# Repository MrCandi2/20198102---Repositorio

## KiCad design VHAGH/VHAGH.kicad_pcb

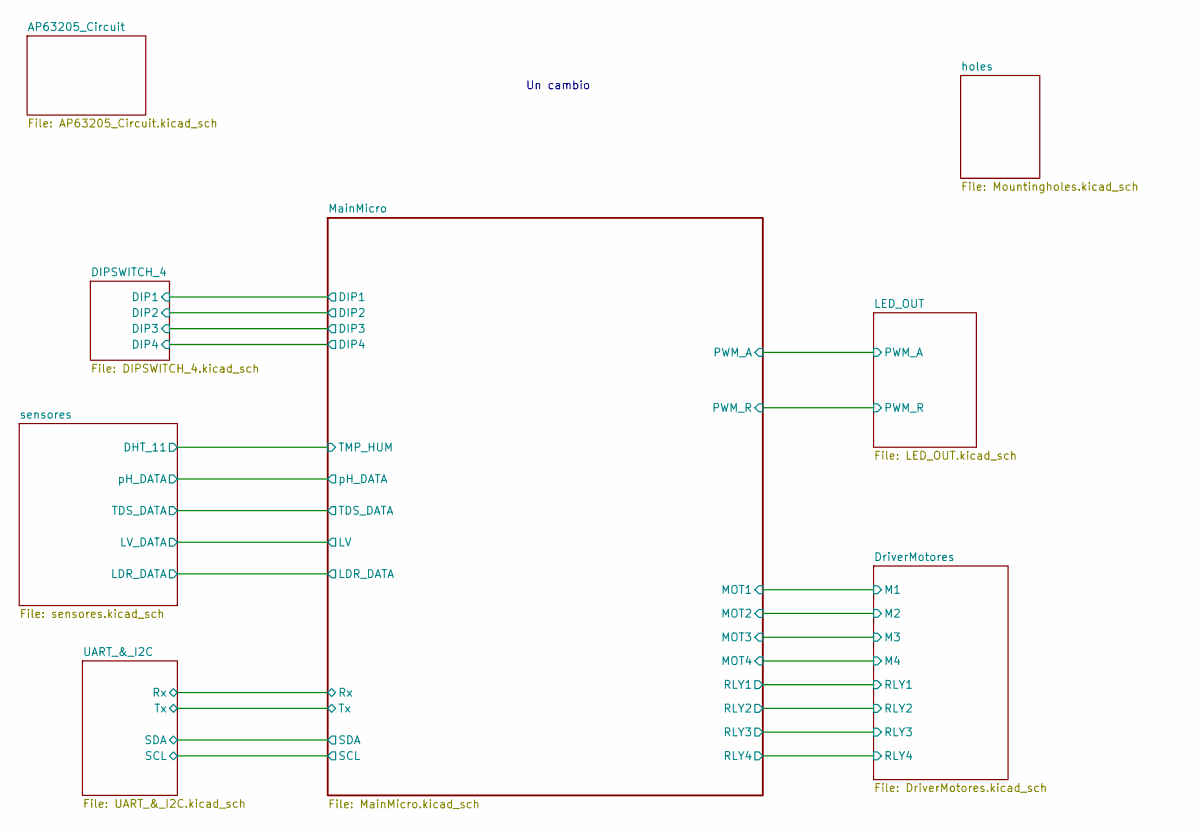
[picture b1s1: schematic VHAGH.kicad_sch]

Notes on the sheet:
Un cambio

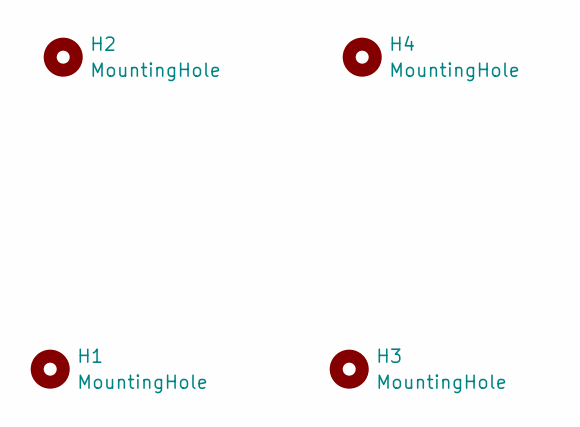
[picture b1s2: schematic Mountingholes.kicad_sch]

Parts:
H1, H2, H3, H4: MountingHole; MountingHole_2.2mm_M2

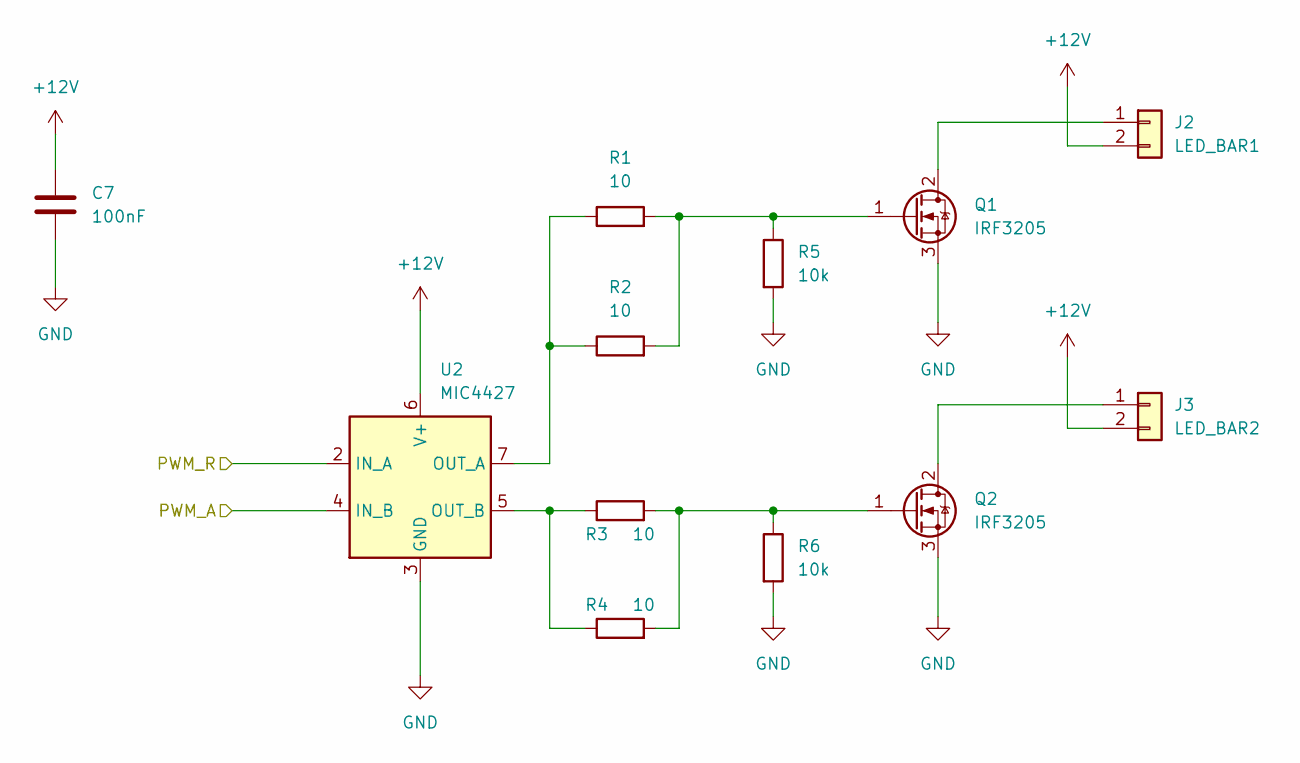
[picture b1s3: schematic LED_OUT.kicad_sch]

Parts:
C7: 100nF; C_0603_1608Metric
J2: LED_BAR1; TerminalBlock_bornier-2_P5.08mm
J3: LED_BAR2; TerminalBlock_bornier-2_P5.08mm
Q1, Q2: IRF3205; TO-220-3_Vertical
R1, R2, R3, R4: 10; R_0603_1608Metric
R5, R6: 10k; R_0603_1608Metric
U2: MIC4427; SOIC-8_3.9x4.9mm_P1.27mm

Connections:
+12V: C7.1, J2.2, J3.2, U2.6 (V+); also elsewhere on the board
/LED_OUT/PWM_A: U2.4 (IN_B); also elsewhere on the board
/LED_OUT/PWM_R: U2.2 (IN_A); also elsewhere on the board
GND: C7.2, Q1.3 (S), Q2.3 (S), R5.2, R6.2, U2.3 (GND); also elsewhere on the board
unnamed: J2.1, Q1.2 (D)
unnamed: J3.1, Q2.2 (D)
unnamed: Q1.1 (G), R1.2, R2.2, R5.1
unnamed: Q2.1 (G), R3.2, R4.2, R6.1
unnamed: R1.1, R2.1, U2.7 (OUT_A)
unnamed: R3.1, R4.1, U2.5 (OUT_B)

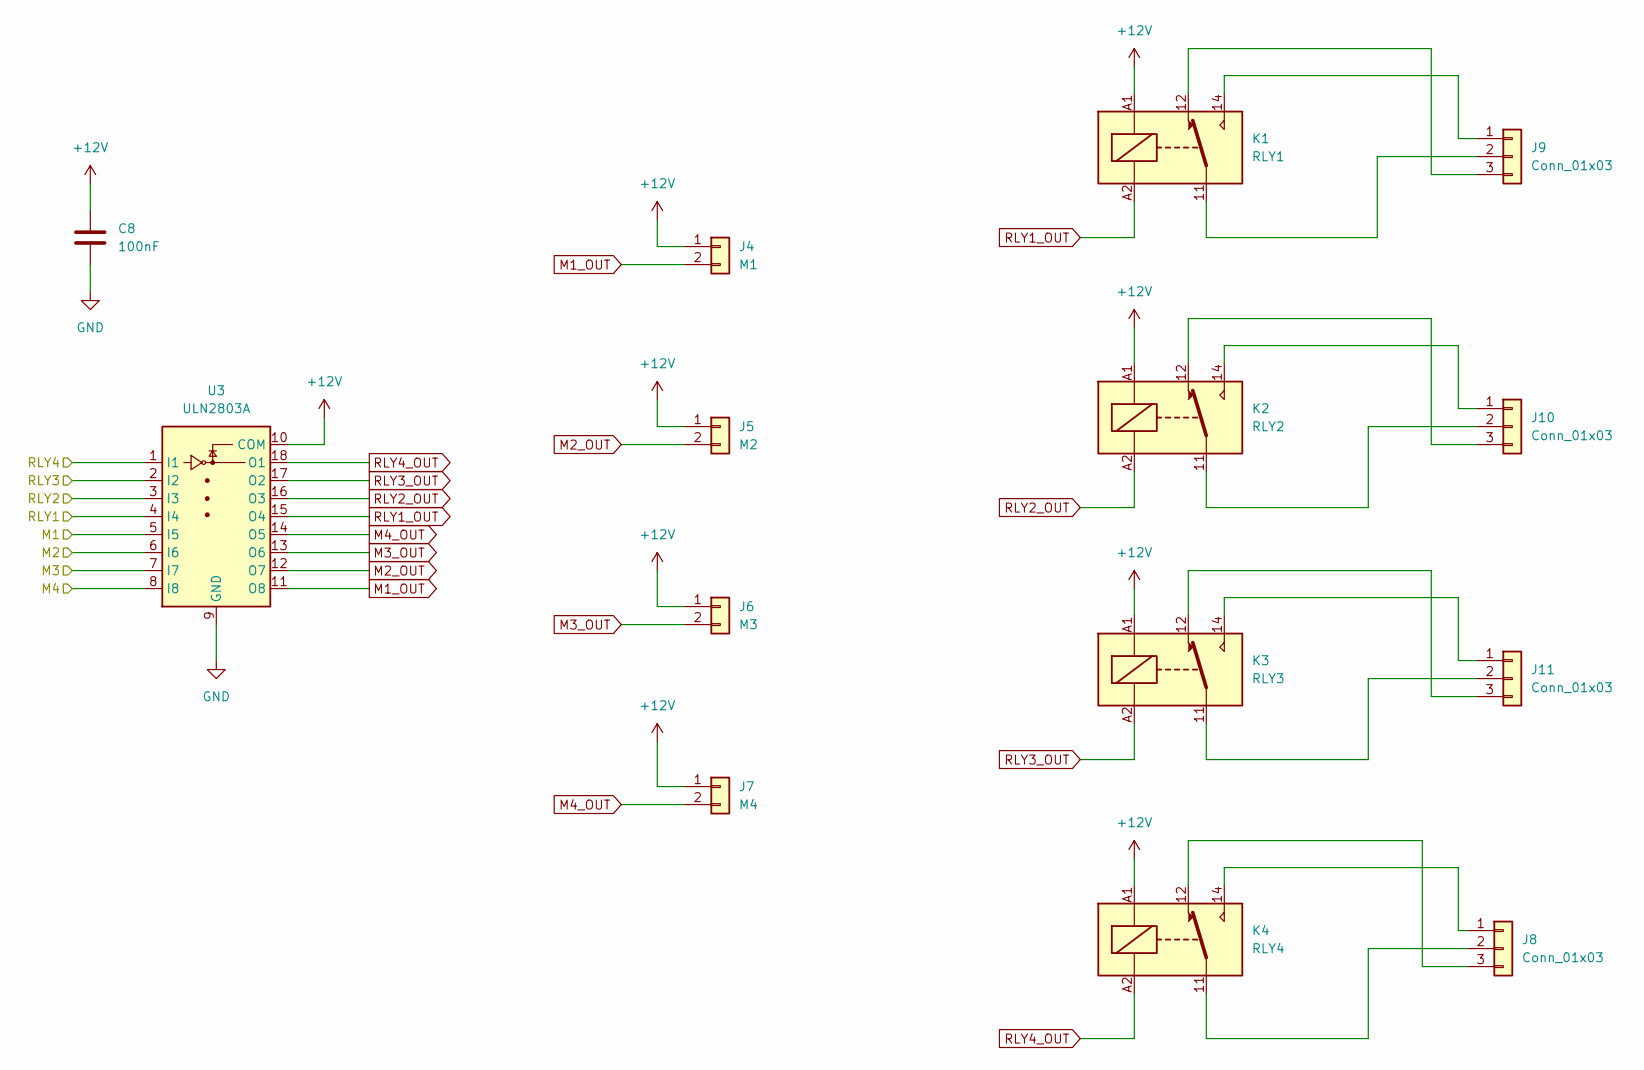
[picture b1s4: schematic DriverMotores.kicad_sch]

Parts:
C8: 100nF; C_0603_1608Metric
J4: M1; TerminalBlock_bornier-2_P5.08mm
J5: M2; TerminalBlock_bornier-2_P5.08mm
J6: M3; TerminalBlock_bornier-2_P5.08mm
J7: M4; TerminalBlock_bornier-2_P5.08mm
J8, J9, J10, J11: Conn_01x03; TerminalBlock_bornier-3_P5.08mm
K1: RLY1; Relay_SPDT_Finder_36.11
K2: RLY2; Relay_SPDT_Finder_36.11
K3: RLY3; Relay_SPDT_Finder_36.11
K4: RLY4; Relay_SPDT_Finder_36.11
U3: ULN2803A; SOIC-18W_7.5x11.6mm_P1.27mm

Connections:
+12V: C8.1, J4.1, J5.1, J6.1, J7.1, K1.A1, K2.A1, K3.A1, K4.A1, U3.10 (COM); also elsewhere on the board
/DriverMotores/M1: U3.5 (I5); also elsewhere on the board
/DriverMotores/M2: U3.6 (I6); also elsewhere on the board
/DriverMotores/M3: U3.7 (I7); also elsewhere on the board
/DriverMotores/M4: U3.8 (I8); also elsewhere on the board
/DriverMotores/RLY1: U3.4 (I4); also elsewhere on the board
/DriverMotores/RLY2: U3.3 (I3); also elsewhere on the board
/DriverMotores/RLY3: U3.2 (I2); also elsewhere on the board
/DriverMotores/RLY4: U3.1 (I1); also elsewhere on the board
GND: C8.2, U3.9 (GND); also elsewhere on the board
M1_OUT: J4.2, U3.11 (O8)
M2_OUT: J5.2, U3.12 (O7)
M3_OUT: J6.2, U3.13 (O6)
M4_OUT: J7.2, U3.14 (O5)
unnamed: J8.1, K4.14
unnamed: J8.2, K4.11
unnamed: J8.3, K4.12
unnamed: J9.1, K1.14
unnamed: J9.2, K1.11
unnamed: J9.3, K1.12
unnamed: J10.1, K2.14
unnamed: J10.2, K2.11
unnamed: J10.3, K2.12
unnamed: J11.1, K3.14
unnamed: J11.2, K3.11
unnamed: J11.3, K3.12
RLY1_OUT: K1.A2, U3.15 (O4)
RLY2_OUT: K2.A2, U3.16 (O3)
RLY3_OUT: K3.A2, U3.17 (O2)
RLY4_OUT: K4.A2, U3.18 (O1)

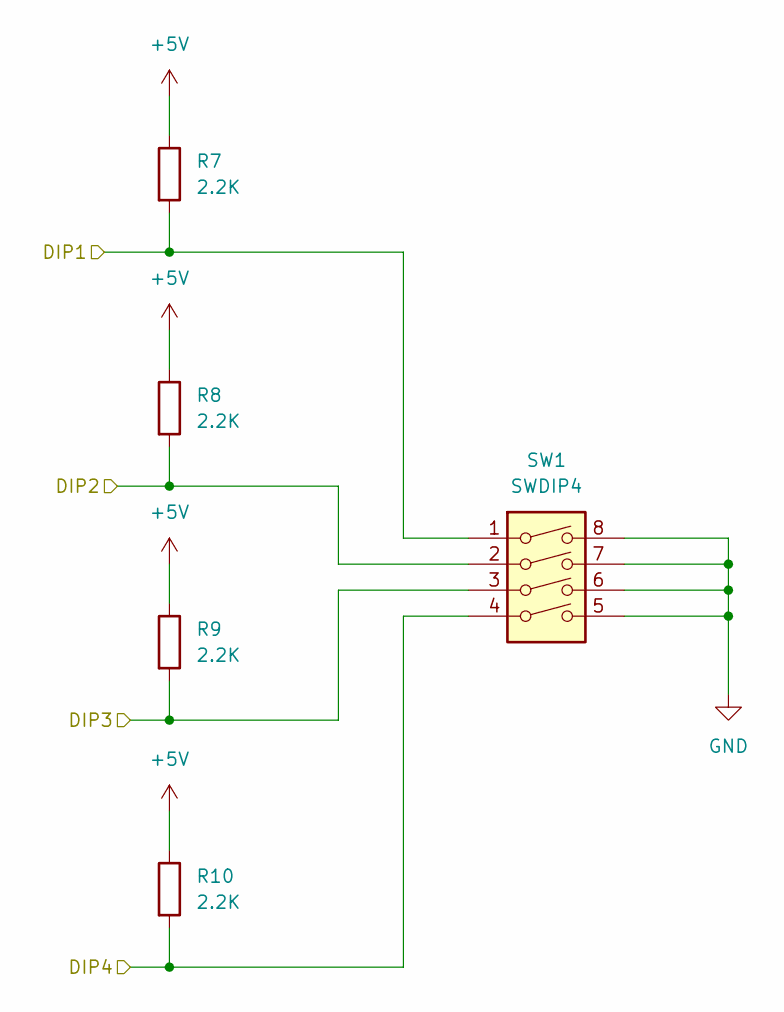
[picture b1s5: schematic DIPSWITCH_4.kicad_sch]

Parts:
R7, R8, R9, R10: 2.2K; R_0603_1608Metric
SW1: SWDIP4; SW_DIP_SPSTx04_Slide_9.78x12.34mm_W8.61mm_P2.54mm

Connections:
+5V: R7.1, R8.1, R9.1, R10.1; also elsewhere on the board
/DIPSWITCH_4/DIP1: R7.2, SW1.1; also elsewhere on the board
/DIPSWITCH_4/DIP2: R8.2, SW1.2; also elsewhere on the board
/DIPSWITCH_4/DIP3: R9.2, SW1.3; also elsewhere on the board
/DIPSWITCH_4/DIP4: R10.2, SW1.4; also elsewhere on the board
GND: SW1.5, SW1.6, SW1.7, SW1.8; also elsewhere on the board

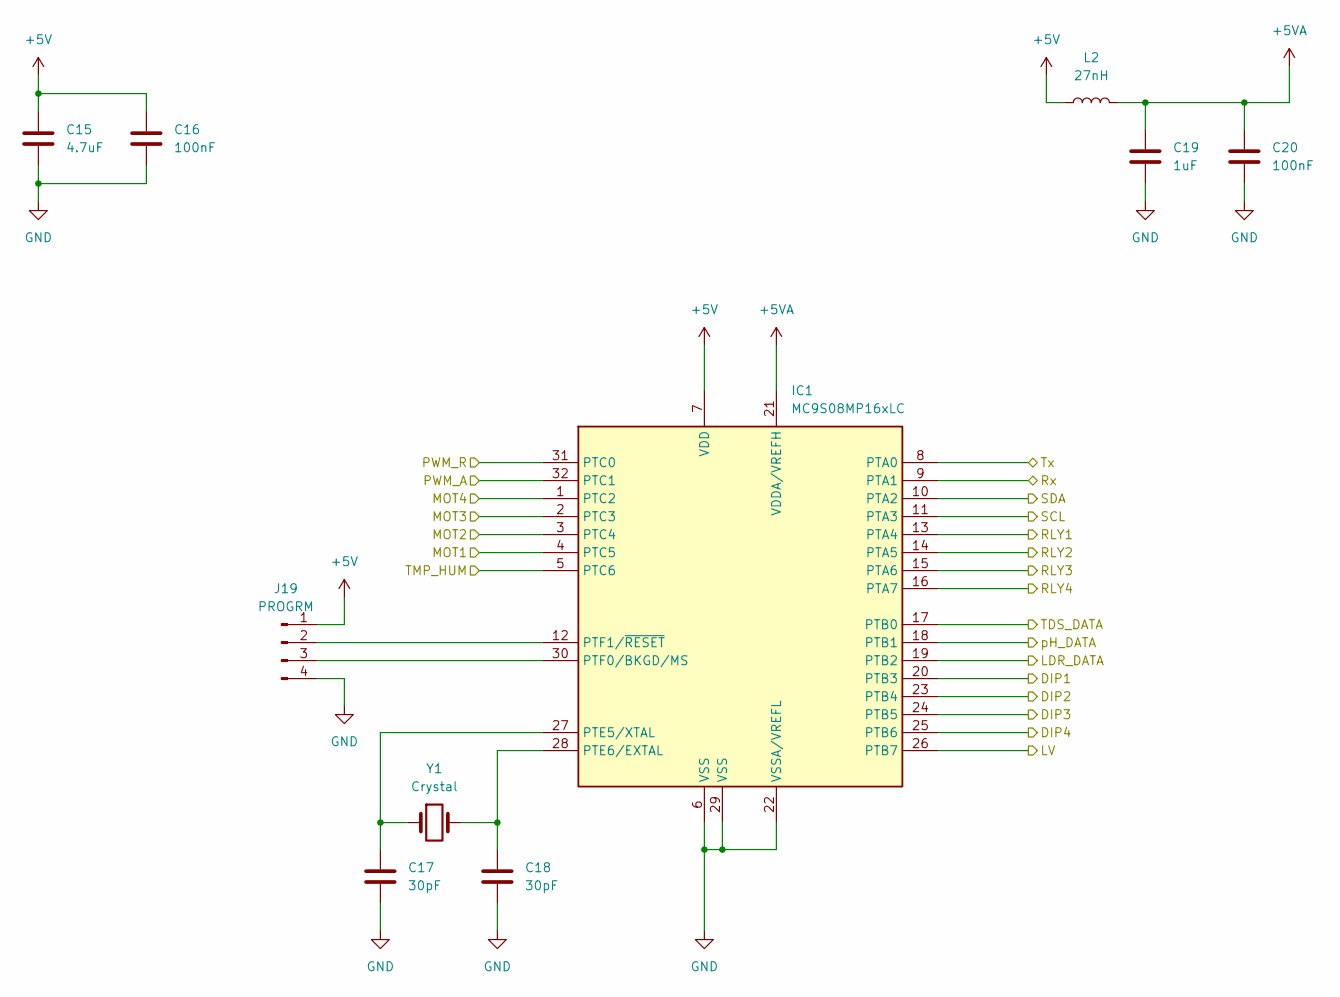
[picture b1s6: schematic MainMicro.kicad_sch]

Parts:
C15: 4.7uF; C_0603_1608Metric
C16, C20: 100nF; C_0603_1608Metric
C17, C18: 30pF; C_0603_1608Metric
C19: 1uF; C_0603_1608Metric
IC1: MC9S08MP16xLC; LQFP-32_7x7mm_P0.8mm
J19: PROGRM; PinHeader_1x04_P2.54mm_Vertical
L2: 27nH; L_0805_2012Metric
Y1: Crystal; Crystal_SMD_2012-2Pin_2.0x1.2mm

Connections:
+5V: C15.1, C16.1, IC1.7 (VDD), J19.1, L2.1; also elsewhere on the board
+5VA: C19.1, C20.1, IC1.21 (VDDA/VREFH), L2.2
/DIPSWITCH_4/DIP1: IC1.20 (PTB3); also elsewhere on the board
/DIPSWITCH_4/DIP2: IC1.23 (PTB4); also elsewhere on the board
/DIPSWITCH_4/DIP3: IC1.24 (PTB5); also elsewhere on the board
/DIPSWITCH_4/DIP4: IC1.25 (PTB6); also elsewhere on the board
/DriverMotores/M1: IC1.4 (PTC5); also elsewhere on the board
/DriverMotores/M2: IC1.3 (PTC4); also elsewhere on the board
/DriverMotores/M3: IC1.2 (PTC3); also elsewhere on the board
/DriverMotores/M4: IC1.1 (PTC2); also elsewhere on the board
/DriverMotores/RLY1: IC1.13 (PTA4); also elsewhere on the board
/DriverMotores/RLY2: IC1.14 (PTA5); also elsewhere on the board
/DriverMotores/RLY3: IC1.15 (PTA6); also elsewhere on the board
/DriverMotores/RLY4: IC1.16 (PTA7); also elsewhere on the board
/LED_OUT/PWM_A: IC1.32 (PTC1); also elsewhere on the board
/LED_OUT/PWM_R: IC1.31 (PTC0); also elsewhere on the board
/MainMicro/LDR_DATA: IC1.19 (PTB2); also elsewhere on the board
/MainMicro/LV: IC1.26 (PTB7); also elsewhere on the board
/MainMicro/Rx: IC1.9 (PTA1); also elsewhere on the board
/MainMicro/SCL: IC1.11 (PTA3); also elsewhere on the board
/MainMicro/SDA: IC1.10 (PTA2); also elsewhere on the board
/MainMicro/TDS_DATA: IC1.17 (PTB0); also elsewhere on the board
/MainMicro/TMP_HUM: IC1.5 (PTC6); also elsewhere on the board
/MainMicro/Tx: IC1.8 (PTA0); also elsewhere on the board
/MainMicro/pH_DATA: IC1.18 (PTB1); also elsewhere on the board
GND: C15.2, C16.2, C17.2, C18.2, C19.2, C20.2, IC1.6 (VSS), IC1.22 (VSSA/VREFL), IC1.29 (VSS), J19.4; also elsewhere on the board
unnamed: C17.1, IC1.27 (PTE5/XTAL), Y1.1
unnamed: C18.1, IC1.28 (PTE6/EXTAL), Y1.2
unnamed: IC1.12 (PTF1/~RESET), J19.2
unnamed: IC1.30 (PTF0/BKGD/MS), J19.3

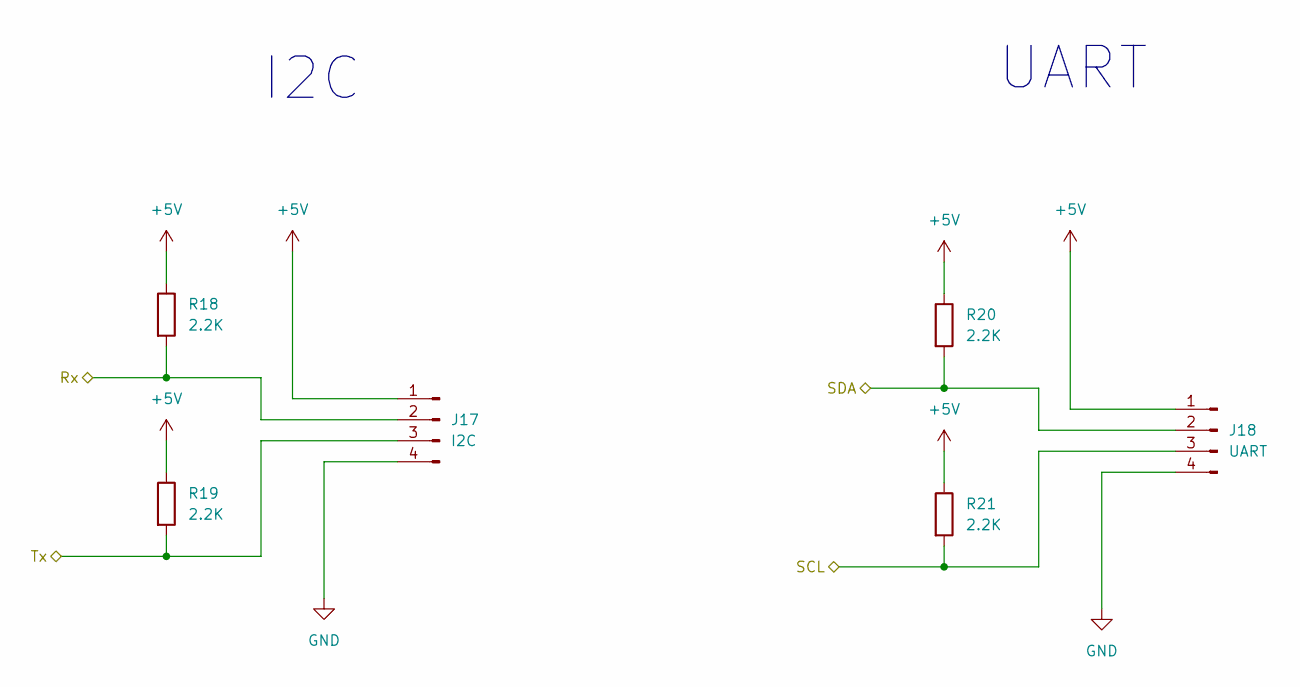
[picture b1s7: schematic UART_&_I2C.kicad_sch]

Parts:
J17: I2C; PinHeader_1x04_P2.54mm_Vertical
J18: UART; PinHeader_1x04_P2.54mm_Vertical
R18, R19, R20, R21: 2.2K; R_0603_1608Metric

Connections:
+5V: J17.1, J18.1, R18.1, R19.1, R20.1, R21.1; also elsewhere on the board
/MainMicro/Rx: J17.2, R18.2; also elsewhere on the board
/MainMicro/SCL: J18.3, R21.2; also elsewhere on the board
/MainMicro/SDA: J18.2, R20.2; also elsewhere on the board
/MainMicro/Tx: J17.3, R19.2; also elsewhere on the board
GND: J17.4, J18.4; also elsewhere on the board

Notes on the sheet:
I2C
UART

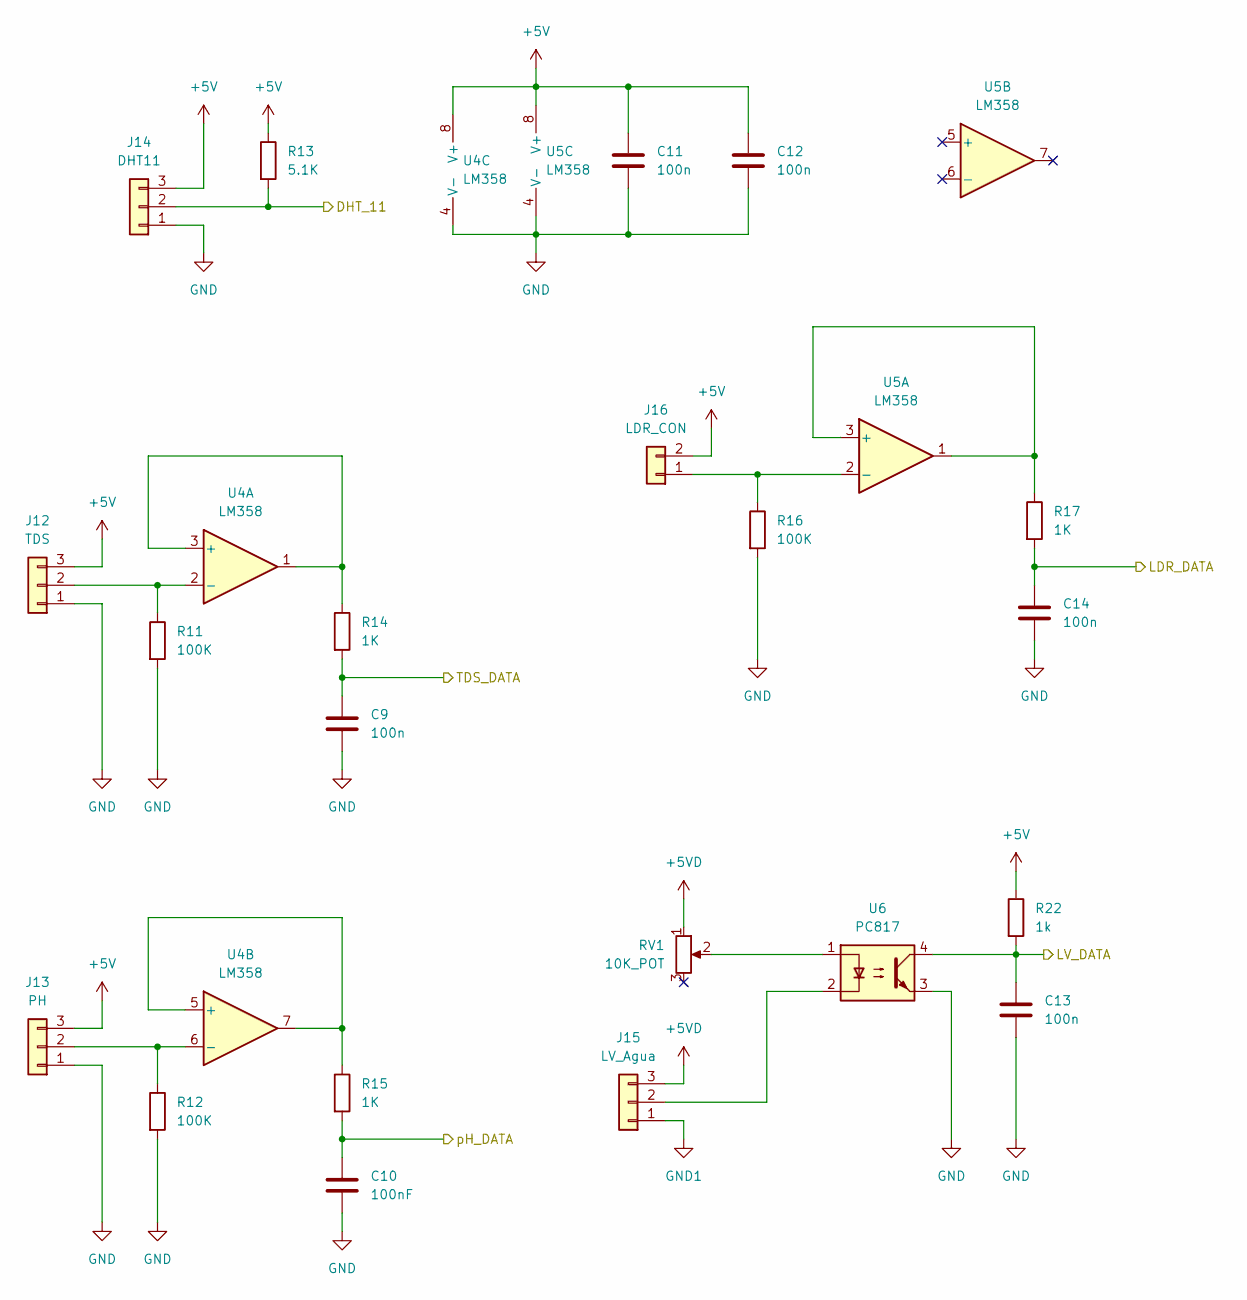
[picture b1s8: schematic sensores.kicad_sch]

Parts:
C9, C11, C12, C13, C14: 100n; C_0603_1608Metric
C10: 100nF; C_0603_1608Metric
J12: TDS; TerminalBlock_bornier-3_P5.08mm
J13: PH; TerminalBlock_bornier-3_P5.08mm
J14: DHT11; TerminalBlock_bornier-3_P5.08mm
J15: LV_Agua; TerminalBlock_bornier-3_P5.08mm
J16: LDR_CON; TerminalBlock_bornier-2_P5.08mm
R11, R12, R16: 100K; R_0603_1608Metric
R13: 5.1K; R_0603_1608Metric
R14, R15, R17: 1K; R_0603_1608Metric
R22: 1k; R_0603_1608Metric
RV1: 10K_POT; Potentiometer_Alps_RK097_Single_Horizontal
U4, U5: LM358; SOIC-8_3.9x4.9mm_P1.27mm
U6: PC817; DIP-4_W7.62mm

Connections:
+5V: C11.1, C12.1, J12.3, J13.3, J14.3, J16.2, R13.1, R22.1, U4.8 (V+), U5.8 (V+); also elsewhere on the board
+5VD: J15.3, RV1.1
/MainMicro/LDR_DATA: C14.1, R17.2; also elsewhere on the board
/MainMicro/LV: C13.1, R22.2, U6.4; also elsewhere on the board
/MainMicro/TDS_DATA: C9.1, R14.2; also elsewhere on the board
/MainMicro/TMP_HUM: J14.2, R13.2; also elsewhere on the board
/MainMicro/pH_DATA: C10.1, R15.2; also elsewhere on the board
GND: C9.2, C10.2, C11.2, C12.2, C13.2, C14.2, J12.1, J13.1, J14.1, R11.2, R12.2, R16.2, U4.4 (V-), U5.4 (V-), U6.3; also elsewhere on the board
GND1: J15.1
unnamed: J12.2, R11.1, U4.2 (-)
unnamed: J13.2, R12.1, U4.6 (-)
unnamed: J15.2, U6.2
unnamed: J16.1, R16.1, U5.2 (-)
unnamed: R14.1, U4.1, U4.3 (+)
unnamed: R15.1, U4.5 (+), U4.7
unnamed: R17.1, U5.1, U5.3 (+)
unnamed: RV1.2, U6.1

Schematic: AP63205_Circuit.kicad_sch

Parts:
C1: 10uF; C_0603_1608Metric
C2, C5, C6: 100nF; C_0603_1608Metric
C3, C4: 22uF; C_0603_1608Metric
J1: +12V; TerminalBlock_bornier-2_P5.08mm
L1: u.7uH; L_0805_2012Metric
U1: AP63205WU; TSOT-23-6

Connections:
+5V: C3.1, C4.1, C5.1, C6.1, L1.2, U1.1 (FB); also elsewhere on the board
+12V: C1.1, J1.2, U1.2 (EN), U1.3 (IN); also elsewhere on the board
GND: C1.2, C3.2, C4.2, C5.2, C6.2, J1.1, U1.4 (GND); also elsewhere on the board
unnamed: C2.1, L1.1, U1.5 (SW)
unnamed: C2.2, U1.6 (BST)

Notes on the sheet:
Capacitor ceramico es suficiente Capacitor low ESR recomendado para minimizar pérdidas
2A Continous Output Current
Capacitor ceramico es suficiente

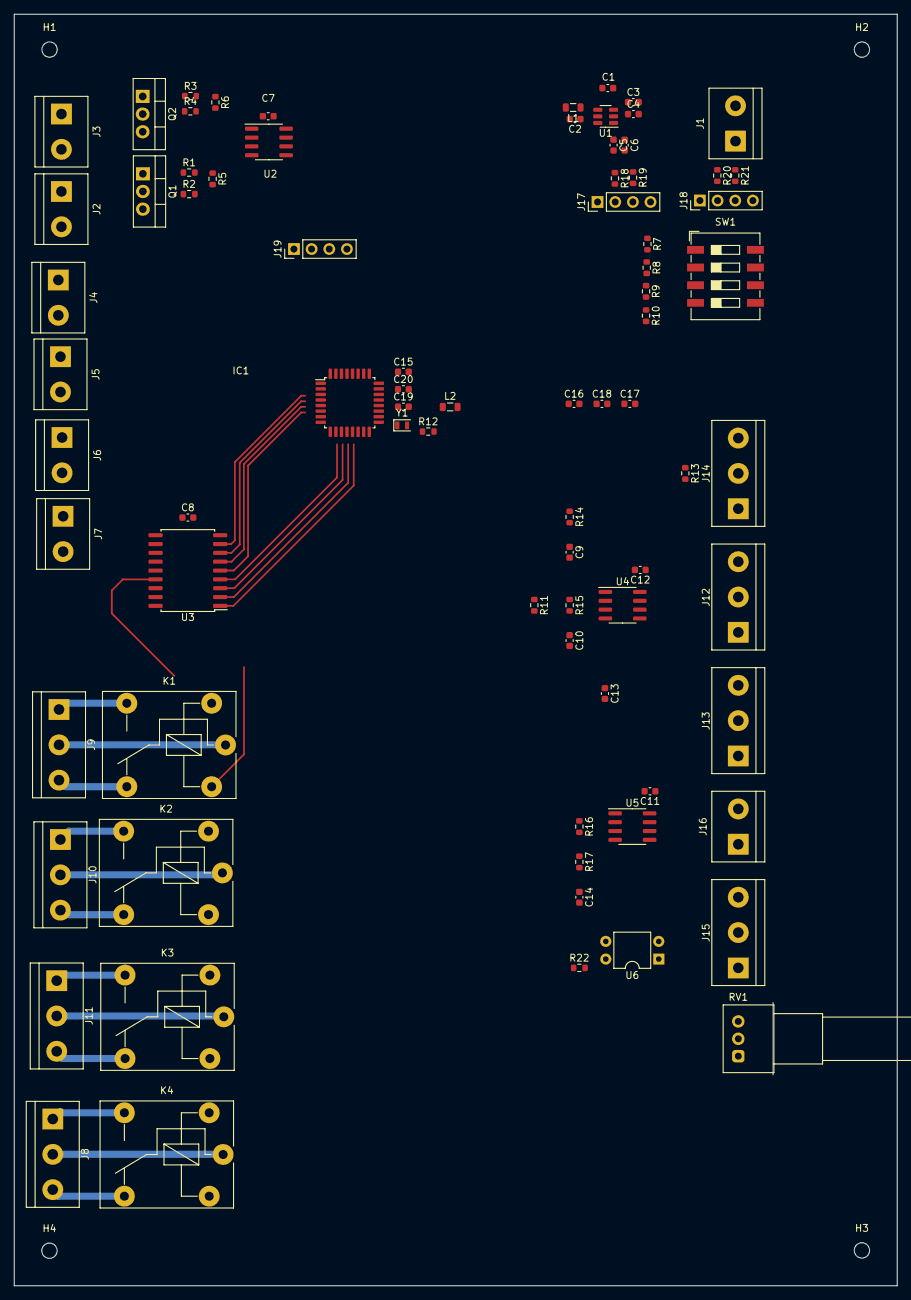
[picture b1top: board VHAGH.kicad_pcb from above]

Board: 2 copper layers, 127.0 x 182.9 mm, 83 parts (0 on the bottom side), 68 nets.

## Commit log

2022-06-03 sdfsdaf
2022-06-10 Add files via upload
    Diseno de logo elegido
2022-06-10 Mis propuestas de diseno de logo
2022-06-10 Add files via upload
    Plantillas de especificacion de requisitos de producto
2022-07-22 Prueba de commit and push
2022-07-22 Diseno PCB
2022-07-22 modificado 7/22/22 6:05pm
2022-07-23 Diseño PCB
